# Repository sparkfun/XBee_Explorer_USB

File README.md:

SparkFun XBee Explorer USB
==========================

[*SparkFun XBee Explorer USB (WRL-11812)*](https://www.sparkfun.com/products/11812)

This is a simple to use, USB to serial base unit for the Digi XBee line. 
This unit works with all XBee modules including the Series 1 and Series 2.5, standard and Pro version. 
Plug the unit into the XBee Explorer, attach a mini USB cable, 
and you will have direct access to the serial and programming pins on the XBee unit.
It has an FT231X USB-to-serial converter on board. 

Repository Contents
-------------------

* **/Hardware** - All Eagle design files (.brd, .sch)
* **/Production** - Test bed files and production panel files

Product Versions
----------------
* [WRL-08687](https://www.sparkfun.com/products/retired/8687)- Hardware version 1.5, with FT232 USB-to-serial converter. Retired

Version History
---------------
* [V_2.1](https://github.com/sparkfun/XBee_Explorer_USB/tree/V_2.1) - GitHub files version 2.1
* [V_1.5](https://github.com/sparkfun/XBee_Explorer_USB/tree/V_1.5) -- GitHub files version 1.5

License Information
-------------------
The hardware is released under [Creative Commons ShareAlike 4.0 International](https://creativecommons.org/licenses/by-sa/4.0/).

Distributed as-is; no warranty is given.

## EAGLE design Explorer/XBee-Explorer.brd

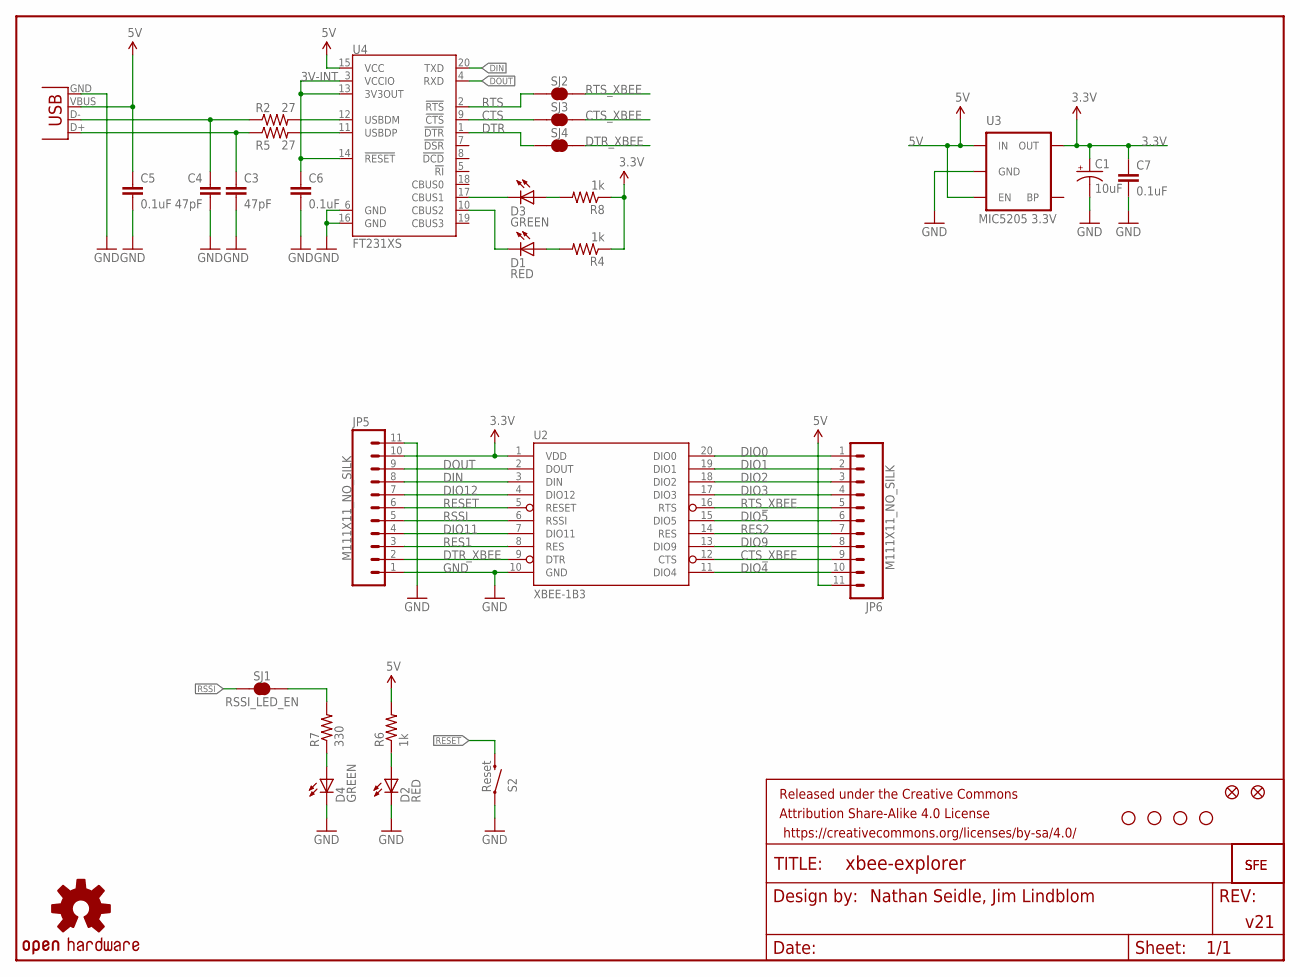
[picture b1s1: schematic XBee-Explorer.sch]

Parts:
C1: 10uF; EIA3216
C3, C4: 47pF; 0603-CAP
C5, C6, C7: 0.1uF; 0603-CAP
D1, D2: RED; LED-0603
D3, D4: GREEN; LED-0603
FRAME1: FRAME-LETTER; CREATIVE_COMMONS
JP1, JP4: FIDUCIAL1X2; FIDUCIAL-1X2
JP5, JP6: M111X11_NO_SILK; 1X11_NO_SILK
LOGO1: OSHW-LOGOS; OSHW-LOGO-S
R2, R5: 27; 0603-RES
R4, R6, R8: 1k; 0603-RES
R7: 330; 0603-RES
S2: Reset; TACTILE_SWITCH_SMD
SJ1: RSSI_LED_EN; SJ_2S-TRACE
SJ2: CTS_EN; SJ_2S-TRACE
SJ3: RTS_EN; SJ_2S-TRACE
SJ4: DTR; SJ_2S-TRACE
U2: XBEE-1B3; XBEE-SMD
U3: MIC5205 3.3V; SOT23-5
U4: FT231XS; SSOP20_L
U$1: LOGO-SFESK; SFE-LOGO-FLAME
U$4: LOGO-SFENEW; SFE-NEW-WEBLOGO
U$5, U$9, U$10, U$11: STAND-OFF
X1: USBSMD; USB-MINIB

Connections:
3.3V: C1.A (+), C7.1, JP5.10, R4.1, R8.1, U2.1 (VDD), U3.5 (OUT)
3V-INT: C6.1, U4.3 (VCCIO), U4.13 (3V3OUT), U4.14 (!RESET)
5V: C5.1, JP6.11, R6.2, U3.1 (IN), U3.3 (EN), U4.15 (VCC), X1.VBUS
CTS: SJ3.1, U4.9 (!CTS)
CTS_XBEE: JP6.9, SJ3.2, U2.12 (CTS)
DIN: JP5.8, U2.3 (DIN), U4.20 (TXD)
DIO0: JP6.1, U2.20 (DIO0)
DIO1: JP6.2, U2.19 (DIO1)
DIO2: JP6.3, U2.18 (DIO2)
DIO3: JP6.4, U2.17 (DIO3)
DIO4: JP6.10, U2.11 (DIO4)
DIO5: JP6.6, U2.15 (DIO5)
DIO9: JP6.8, U2.13 (DIO9)
DIO11: JP5.4, U2.7 (DIO11)
DIO12: JP5.7, U2.4 (DIO12)
DOUT: JP5.9, U2.2 (DOUT), U4.4 (RXD)
DTR: SJ4.1, U4.1 (!DTR)
DTR_XBEE: JP5.2, SJ4.2, U2.9 (DTR)
GND: C1.C (-), C3.2, C4.2, C5.2, C6.2, C7.2, D2.C, D4.C, JP5.1, JP5.11, S2.1, U2.10 (GND), U3.2 (GND), U4.6 (GND), U4.16 (GND), X1.GND
unnamed: D1.A, R4.2
unnamed: D4.A, R7.1
unnamed: C3.1, R5.1, X1.D+
unnamed: D3.A, R8.2
unnamed: C4.1, R2.1, X1.D-
unnamed: D3.C, U4.17 (CBUS1)
unnamed: R5.2, U4.11 (USBDP)
unnamed: R2.2, U4.12 (USBDM)
unnamed: R7.2, SJ1.2
unnamed: D2.A, R6.1
RES1: JP5.3, U2.8 (RES)
RES2: JP6.7, U2.14 (RES)
RESET: JP5.6, S2.3 (2), U2.5 (RESET)
RSSI: JP5.5, SJ1.1, U2.6 (RSSI)
RTS: SJ2.1, U4.2 (!RTS)
RTS_XBEE: JP6.5, SJ2.2, U2.16 (RTS)
TXLED: D1.C, U4.10 (CBUS2)

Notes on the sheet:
Nathan Seidle, Jim Lindblom
v21

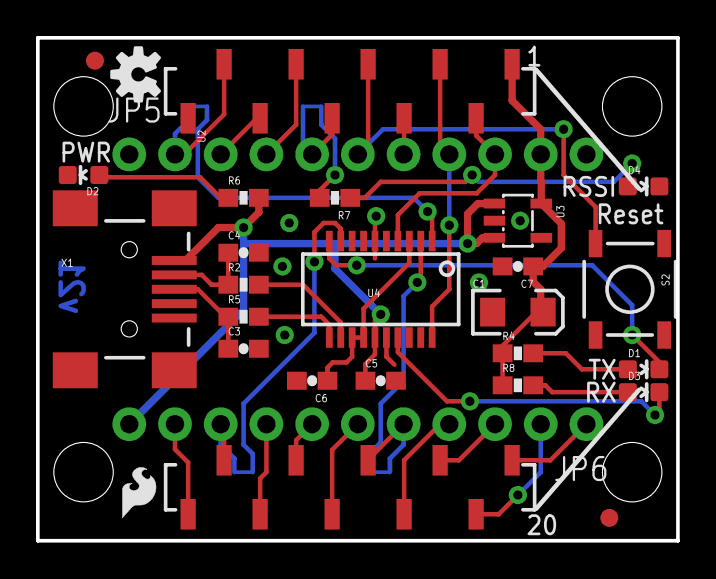
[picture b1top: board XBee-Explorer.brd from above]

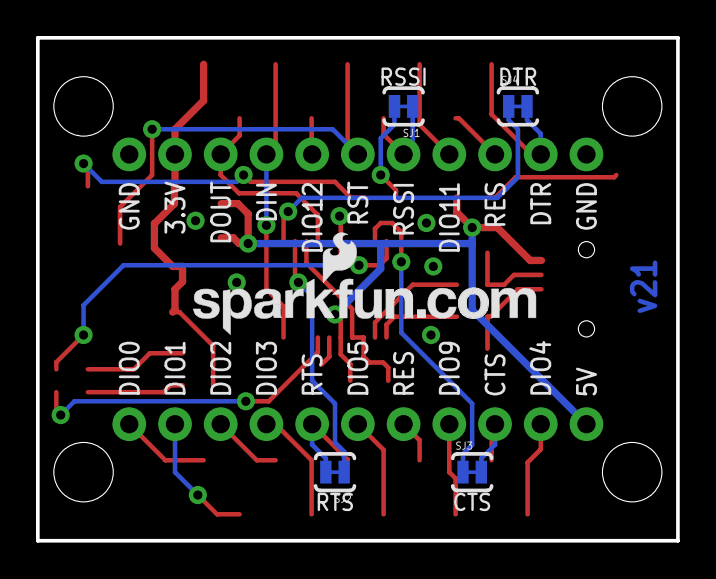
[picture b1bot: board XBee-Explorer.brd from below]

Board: 2 copper layers, 35.6 x 27.9 mm, 37 parts (5 on the bottom side), 36 nets.

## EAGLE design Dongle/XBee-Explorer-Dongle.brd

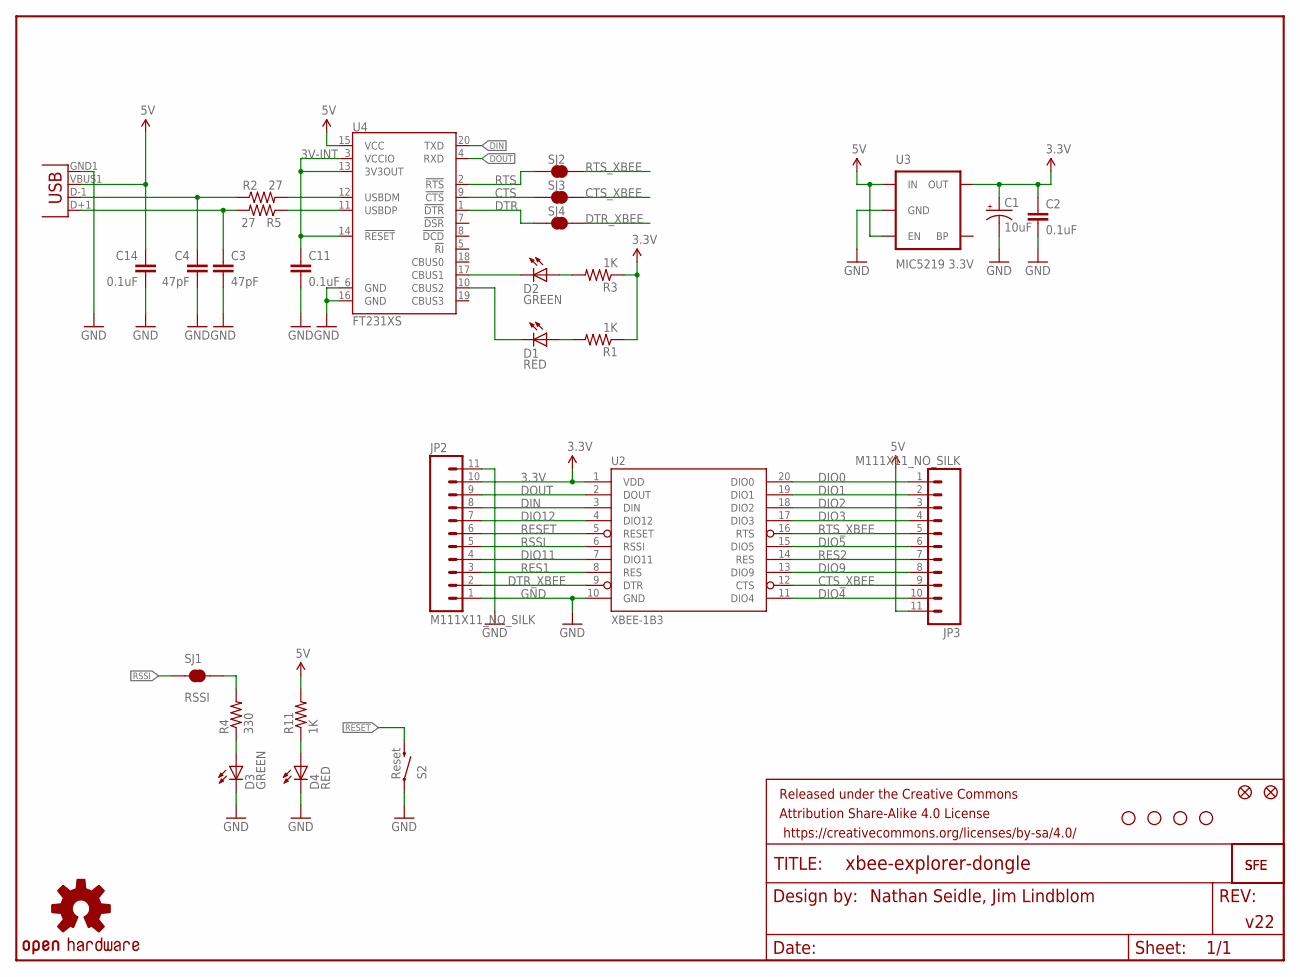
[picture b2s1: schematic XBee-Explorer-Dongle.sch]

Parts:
C1: 10uF; EIA3216
C2, C11, C14: 0.1uF; 0603-CAP
C3, C4: 47pF; 0603-CAP
D1, D4: RED; LED-0603
D2, D3: GREEN; LED-0603
FID1, FID2: FIDUCIAL1X2; FIDUCIAL-1X2
FRAME1: FRAME-LETTER; CREATIVE_COMMONS
JP1: USBA-SMD-MALE-LOCKING; USB-A-SMT-MALE-LOCKING
JP2, JP3: M111X11_NO_SILK; 1X11_NO_SILK
R1, R3, R11: 1K; 0603-RES
R2, R5: 27; 0603-RES
R4: 330; 0603-RES
S2: Reset; TACTILE_SWITCH_SMD
SJ1, SJ2, SJ3, SJ4: RSSI; SJ_2S-TRACE
U2: XBEE-1B3; XBEE-SMD
U3: MIC5219 3.3V; SOT23-5
U4: FT231XS; SSOP20_L
U$1: LOGO-SFESK; SFE-LOGO-FLAME
U$4: LOGO-SFENEW; SFE-NEW-WEBLOGO
U$5, U$9, U$10, U$11: STAND-OFF
U$7: OSHW-LOGOS; OSHW-LOGO-S

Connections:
3.3V: C1.A (+), C2.1, JP2.10, R1.1, R3.1, U2.1 (VDD), U3.5 (OUT)
3V-INT: C11.1, U4.3 (VCCIO), U4.13 (3V3OUT), U4.14 (!RESET)
5V: C14.1, JP1.VBUS1 (VBUS), JP3.11, R11.2, U3.1 (IN), U3.3 (EN), U4.15 (VCC)
CTS: SJ3.1, U4.9 (!CTS)
CTS_XBEE: JP3.9, SJ3.2, U2.12 (CTS)
DIN: JP2.8, U2.3 (DIN), U4.20 (TXD)
DIO0: JP3.1, U2.20 (DIO0)
DIO1: JP3.2, U2.19 (DIO1)
DIO2: JP3.3, U2.18 (DIO2)
DIO3: JP3.4, U2.17 (DIO3)
DIO4: JP3.10, U2.11 (DIO4)
DIO5: JP3.6, U2.15 (DIO5)
DIO9: JP3.8, U2.13 (DIO9)
DIO11: JP2.4, U2.7 (DIO11)
DIO12: JP2.7, U2.4 (DIO12)
DOUT: JP2.9, U2.2 (DOUT), U4.4 (RXD)
DTR: SJ4.1, U4.1 (!DTR)
DTR_XBEE: JP2.2, SJ4.2, U2.9 (DTR)
GND: C1.C (-), C2.2, C3.2, C4.2, C11.2, C14.2, D3.C, D4.C, JP1.GND1 (GND), JP2.1, JP2.11, S2.1, U2.10 (GND), U3.2 (GND), U4.6 (GND), U4.16 (GND)
unnamed: D1.A, R1.2
unnamed: D3.A, R4.1
unnamed: C4.1, JP1.D-1 (D-), R2.1
unnamed: D2.A, R3.2
unnamed: R2.2, U4.12 (USBDM)
unnamed: C3.1, JP1.D+1 (D+), R5.2
unnamed: R5.1, U4.11 (USBDP)
unnamed: R4.2, SJ1.2
unnamed: D4.A, R11.1
RES1: JP2.3, U2.8 (RES)
RES2: JP3.7, U2.14 (RES)
RESET: JP2.6, S2.3 (2), U2.5 (RESET)
RSSI: JP2.5, SJ1.1, U2.6 (RSSI)
RTS: SJ2.1, U4.2 (!RTS)
RTS_XBEE: JP3.5, SJ2.2, U2.16 (RTS)
RXLED: D2.C, U4.17 (CBUS1)
TXLED: D1.C, U4.10 (CBUS2)

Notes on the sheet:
Nathan Seidle, Jim Lindblom
v22

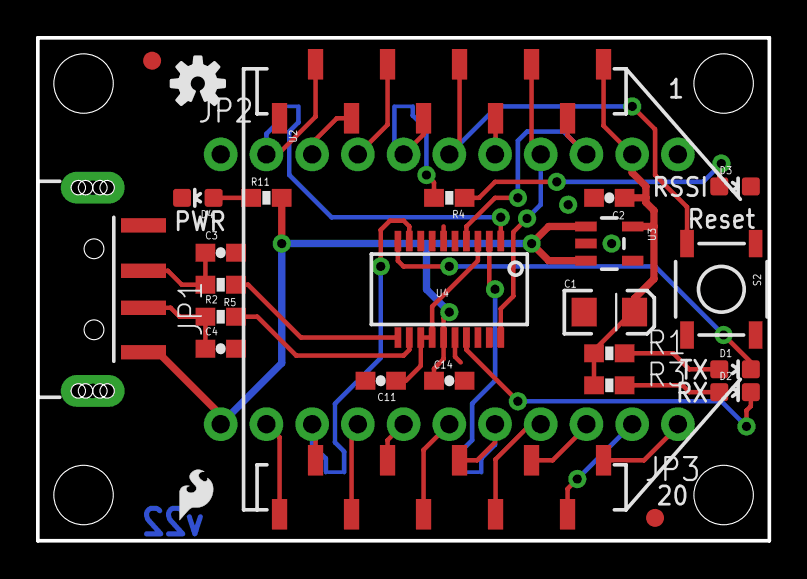
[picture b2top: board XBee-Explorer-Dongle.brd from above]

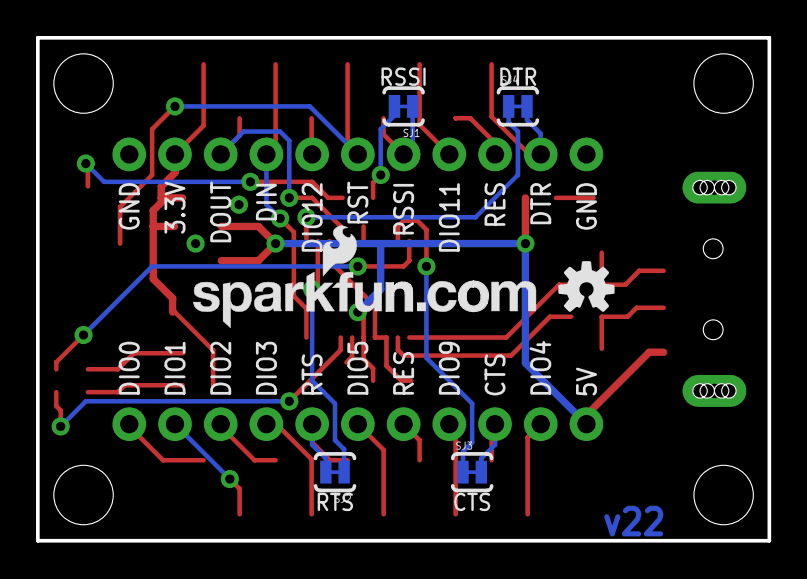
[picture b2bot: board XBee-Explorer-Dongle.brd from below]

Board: 2 copper layers, 40.6 x 27.9 mm, 38 parts (6 on the bottom side), 36 nets.

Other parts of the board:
U$8: OSHW-LOGOS; OSHW-LOGO-S

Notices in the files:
parts and their libraries:
SparkFun-Connectors: Licensing: CC v3.0 Share-Alike You are welcome to use this library for commercial purposes.
SparkFun-Aesthetics: Released under the Creative Commons Attribution Share-Alike 4.0 License
SparkFun-Aesthetics: Released under the Creative Commons
